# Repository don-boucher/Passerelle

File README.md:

# Passerelle
```
+-----------------------------------+

|           nRF7002 DK              |
|  +-----------------------------+  |
|  |    nRF5340 Application Core |  |
|  |     (Main Host Controller)  |  |
|  +------+------------------+---+  |
|         | (QSPI)           |      |
|         |                  | (IPC)|
|  +------v------+    +------v----+ |
|  |   nRF7002   |    |  nRF5340  | |
|  | (Wi-Fi 6 IC)|    |NetworkCore| |
|  +-------------+    | (BLE Stack| |
+-----------------+   +-----------+ +
                    |     
            UART | (with Hardware Flow Control)
                    | 
+-----------------v-----------------+

|           nRF9151 DK              |
|  +-----------------------------+  |
|  |    nRF9151 Cortex-M33 Core  |  |
|  |  (Running Serial LTE Modem) |  |
|  +-----------------------------+  |
+-----------------------------------+
```

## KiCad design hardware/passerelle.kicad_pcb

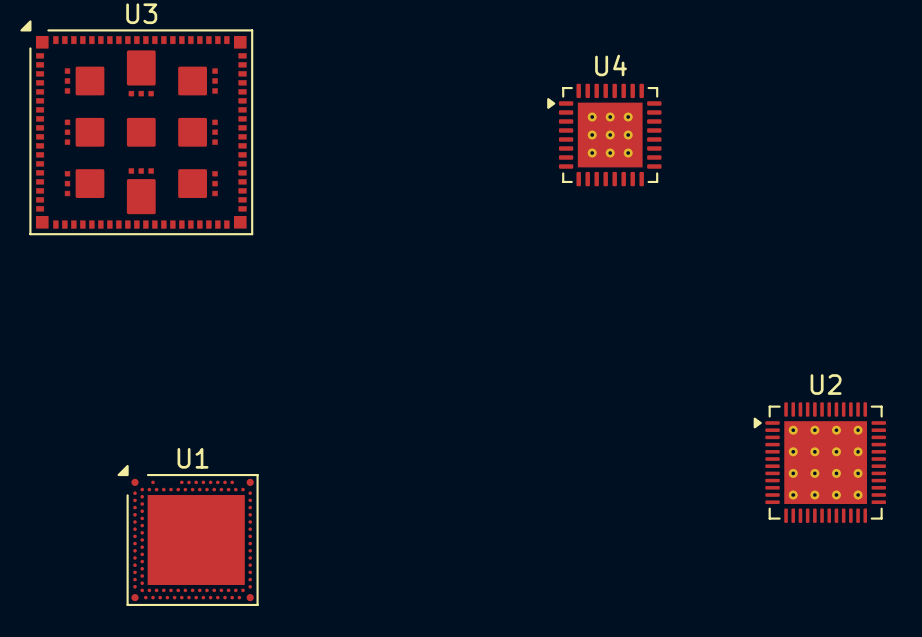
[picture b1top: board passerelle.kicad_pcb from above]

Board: 2 copper layers, 4 parts (0 on the bottom side), 5 nets, no tracks yet.

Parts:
U1: nRF5340-QKxx; Nordic_AQFN-94-1EP_7x7mm_P0.4mm
U2: nRF7002-QFXX; QFN-48-1EP_6x6mm_P0.4mm_EP4.6x4.6mm_ThermalVias
U3: nRF9151-LAXX; LGA_9151_12.1x11.1mm
U4: nPM1300-QEXX; QFN-32-1EP_5x5mm_P0.5mm_EP3.6x3.6mm_ThermalVias

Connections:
GND: U4.2 (PVSS1), U4.6 (PVSS2), U4.16 (VSET2), U4.17 (VSET1), U4.18 (NTC), U4.28 (LSIN1/VINLDO1), U4.29 (LSOUT1/VOUTLDO1), U4.30 (LSIN2/VINLDO2), U4.31 (LSOUT2/VOUTLDO2), U4.33 (AVSS)
unnamed: U1.A19 (VDD), U1.AC1 (VDD), U1.AG1 (VDD), U1.AJ31 (VDD), U1.AL3 (VDD), U1.AL7 (VDD), U1.AL11 (VDD), U1.AL17 (VDD), U1.AL25 (VDD), U1.B8 (VDD), U1.B28 (VDD), U1.C1 (VDD), U1.E31 (VDD), U1.L1 (VDD), U1.N31 (VDD), U1.U1 (VDD)
unnamed: U2.27 (BUCKVSS), U2.28 (BUCKVSS), U2.47 (VSS), U2.49 (EP)
unnamed: U3.1 (GND), U3.7 (GND), U3.13 (GND), U3.15 (GND), U3.20 (GND), U3.25 (GND), U3.30 (GND), U3.34 (GND), U3.36 (GND), U3.38 (GND), U3.39 (GND), U3.40 (GND), U3.41 (GND), U3.43 (GND), U3.46 (GND), U3.51 (GND), U3.55 (GND), U3.60 (GND), U3.66 (GND), U3.71 (GND), U3.76 (GND), U3.105 (GND), U3.106 (GND), U3.107 (GND), U3.108 (GND), U3.109 (GND), U3.110 (GND), U3.111 (GND), U3.112 (GND), U3.113 (GND)
VDD: U4.1 (VOUT1), U4.4 (PVDD), U4.20 (VSYS), U4.32 (VOUT2)

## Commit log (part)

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2026-06-23 add kicad project
2026-06-23 add docs using Git LFS
2026-06-23 switch nRF9161 for nRF9151
2026-06-25 power
2026-06-29 west update
2026-06-29 west zephyr-export
2026-06-29 add zephyr directory as submodule
2026-06-29 add template project
2026-06-29 successful build and flash
2026-06-29 rm zephyr_test
2026-06-29 fix missing application dir
2026-06-29 add .west
2026-06-29 clean build
2026-06-29 blinky (#1)
    * west update
    * west zephyr-export
    * add zephyr directory as submodule
    * ...
    * add template project
    * successful build and flash
2026-06-29 debug instructions
2026-06-30 add digikey intro to zephyr
